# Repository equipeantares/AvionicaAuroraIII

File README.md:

AAA                                                                                                      IIIIIIIIIIIIIIIIIIIIIIIIIIIIII
              A:::A                                                                                                     I::::::::II::::::::II::::::::I
             A:::::A                                                                                                    I::::::::II::::::::II::::::::I
            A:::::::A                                                                                                   II::::::IIII::::::IIII::::::II
           A:::::::::A        uuuuuu    uuuuuu rrrrr   rrrrrrrrr      ooooooooooo   rrrrr   rrrrrrrrr   aaaaaaaaaaaaa     I::::I    I::::I    I::::I  
          A:::::A:::::A       u::::u    u::::u r::::rrr:::::::::r   oo:::::::::::oo r::::rrr:::::::::r  a::::::::::::a    I::::I    I::::I    I::::I  
         A:::::A A:::::A      u::::u    u::::u r:::::::::::::::::r o:::::::::::::::or:::::::::::::::::r aaaaaaaaa:::::a   I::::I    I::::I    I::::I  
        A:::::A   A:::::A     u::::u    u::::u rr::::::rrrrr::::::ro:::::ooooo:::::orr::::::rrrrr::::::r         a::::a   I::::I    I::::I    I::::I  
       A:::::A     A:::::A    u::::u    u::::u  r:::::r     r:::::ro::::o     o::::o r:::::r     r:::::r  aaaaaaa:::::a   I::::I    I::::I    I::::I  
      A:::::AAAAAAAAA:::::A   u::::u    u::::u  r:::::r     rrrrrrro::::o     o::::o r:::::r     rrrrrrraa::::::::::::a   I::::I    I::::I    I::::I  
     A:::::::::::::::::::::A  u::::u    u::::u  r:::::r            o::::o     o::::o r:::::r           a::::aaaa::::::a   I::::I    I::::I    I::::I  
    A:::::AAAAAAAAAAAAA:::::A u:::::uuuu:::::u  r:::::r            o::::o     o::::o r:::::r          a::::a    a:::::a   I::::I    I::::I    I::::I  
   A:::::A             A:::::Au:::::::::::::::uur:::::r            o:::::ooooo:::::o r:::::r          a::::a    a:::::a II::::::IIII::::::IIII::::::II
  A:::::A               A:::::Au:::::::::::::::ur:::::r            o:::::::::::::::o r:::::r          a:::::aaaa::::::a I::::::::II::::::::II::::::::I
 A:::::A                 A:::::Auu::::::::uu:::ur:::::r             oo:::::::::::oo  r:::::r           a::::::::::aa:::aI::::::::II::::::::II::::::::I
AAAAAAA                   AAAAAAA uuuuuuuu  uuuurrrrrrr               ooooooooooo    rrrrrrr            aaaaaaaaaa  aaaaIIIIIIIIIIIIIIIIIIIIIIIIIIIIII

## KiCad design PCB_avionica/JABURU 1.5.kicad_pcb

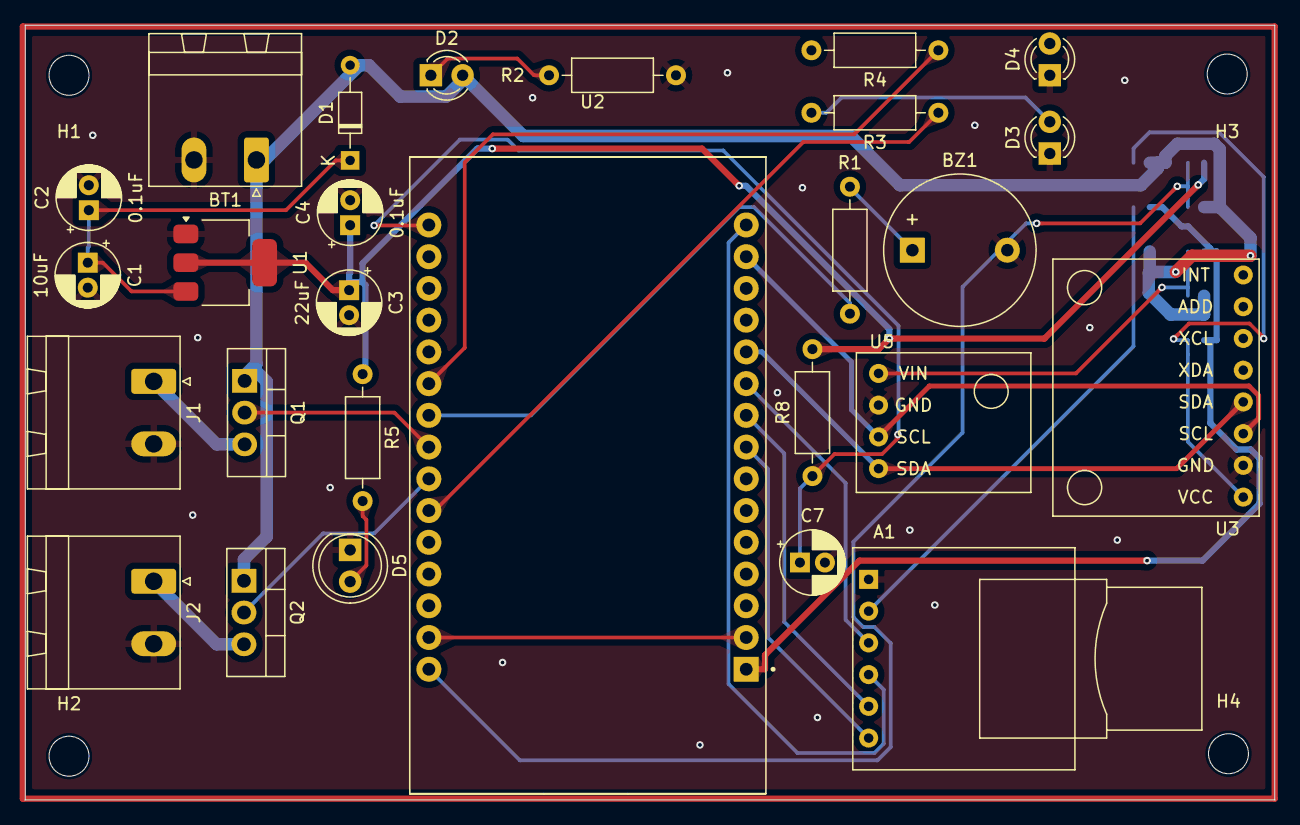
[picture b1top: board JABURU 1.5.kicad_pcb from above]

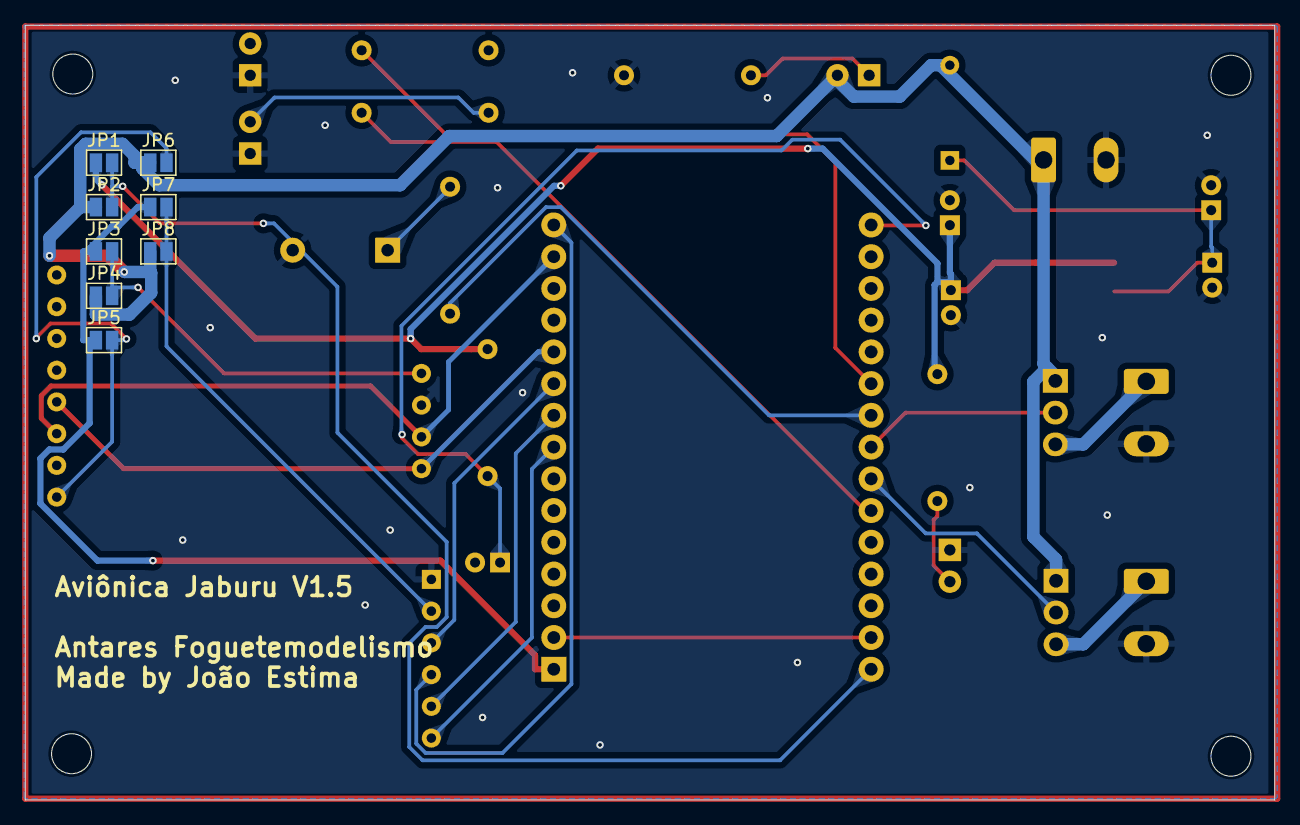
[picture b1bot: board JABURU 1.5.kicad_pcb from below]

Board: 2 copper layers, 100.0 x 62.0 mm, 39 parts (8 on the bottom side), 29 nets.

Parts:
A1: SD_Card_Module
BT1: Battery_Cell; PhoenixContact_MSTBA_2,5_2-G_1x02_P5.00mm_Horizontal
BZ1: Buzzer; Buzzer_12x9.5RM7.6
C1: 10uF; CP_Radial_D5.0mm_P2.00mm
C2, C4, C7: 0.1uF; CP_Radial_D5.0mm_P2.00mm
C3: 22uF; CP_Radial_D5.0mm_P2.00mm
D1: D; D_DO-34_SOD68_P7.62mm_Horizontal
D2: Red; LED_D3.0mm
D3: Yellow; LED_D3.0mm
D4: Green; LED_D3.0mm
D5: LED; LED_D5.0mm
H1, H2, H3, H4: MountingHole; MountingHole_3.2mm_M3
J1: IGN_01; PhoenixContact_MSTBA_2,5_2-G_1x02_P5.00mm_Horizontal
J2: IGN_02; PhoenixContact_MSTBA_2,5_2-G_1x02_P5.00mm_Horizontal
JP1: LDO 3V3; SolderJumper-2_P1.3mm_Open_Pad1.0x1.5mm
JP2, JP4, JP6, JP8: BATTERY; SolderJumper-2_P1.3mm_Open_Pad1.0x1.5mm
JP3, JP5, JP7: ESP 3V3; SolderJumper-2_P1.3mm_Open_Pad1.0x1.5mm
Q1, Q2: NMOS_Substrate; TO-220-3_Vertical
R1: 100; R_Axial_DIN0207_L6.3mm_D2.5mm_P10.16mm_Horizontal
R2, R5: 220; R_Axial_DIN0207_L6.3mm_D2.5mm_P10.16mm_Horizontal
R3, R4: 125; R_Axial_DIN0207_L6.3mm_D2.5mm_P10.16mm_Horizontal
R8: 10K; R_Axial_DIN0207_L6.3mm_D2.5mm_P10.16mm_Horizontal
U1: AMS1117-3.3; SOT-223-3_TabPin2
U2: ESP32-DEVKIT-V1; MODULE_ESP32_DEVKIT_V1
U3: module_mpu6050
U5: module_bme280_alt

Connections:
+3V3: C3.1, C4.1, JP1.1 (A), R5.1, R8.2, U1.2 (VO)
+BATT: BT1.1 (+), D1.2 (A), D2.2 (A), JP2.1 (A), JP4.1 (A), JP6.1 (A), JP8.1 (A), Q1.1 (D), Q2.1 (D)
BZR: R1.1, U2.22 (D33)
CSSD: A1.6 (CS), U2.8 (D5)
GND: A1.1 (GND), BT1.2 (-), BZ1.2 (+), C1.2, C2.2, C3.2, C4.2, C7.2, D3.1 (K), D4.1 (K), D5.1 (K), J1.2, J2.2, R2.1, U1.1 (GND), U3.2 (GND), U5.2 (GND)
IGN_1: Q1.2 (G), U2.23 (D25)
IGN_2: Q2.2 (G), U2.24 (D26)
LedAcionamento: R4.1, U2.21 (D32)
LedStatus: R3.1, U2.25 (D27)
MISO: A1.3 (MISO), U2.10 (D19)
MOSI: A1.4 (MOSI), U2.15 (D23)
unnamed: A1.2 (3V3), JP7.2 (B), JP8.2 (B)
unnamed: BZ1.1 (-), R1.2
unnamed: C1.1, C2.1, D1.1 (K), U1.3 (VI)
unnamed: D2.1 (K), R2.2
unnamed: D3.2 (A), R3.2
unnamed: D4.2 (A), R4.2
unnamed: D5.2 (A), R5.2
unnamed: J1.1, Q1.3 (S)
unnamed: J2.1, Q2.3 (S)
unnamed: JP1.2 (B), JP2.2 (B), U2.30 (VIN)
unnamed: JP3.2 (B), JP4.2 (B), U5.1 (VIN)
unnamed: JP5.2 (B), JP6.2 (B), U3.1 (VCC)
unnamed: C7.1, R8.1, U2.16 (EN)
unnamed: U2.2 (GND), U2.29 (GND)
SCK: A1.5 (CLK), U2.9 (D18)
SCL: U2.14 (D22), U3.3 (SCL), U5.3 (SCL)
SDA: U2.11 (D21), U3.4 (SDA), U5.4 (SDA)
VDD: JP3.1 (A), JP5.1 (A), JP7.1 (A), U2.1 (3V3)

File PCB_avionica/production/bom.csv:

Designator,Footprint,Quantity,Value,LCSC Part #
A1,SD_Card_Module,1,SD_Card_Module,
A2,BMP280_Module,1,BMP280_Module,
BT1,"PhoenixContact_MSTBA_2,5_2-G_1x02_P5.00mm_Horizontal",1,Battery_Cell,
BZ1,Buzzer_12x9.5RM7.6,1,Buzzer,
"C1, C3",CP_Radial_D5.0mm_P2.00mm,2,10uF,
"C2, C4",CP_Radial_D5.0mm_P2.00mm,2,0.1uF,
C5,CP_Radial_D5.0mm_P2.00mm,1,100n,
D1,D_DO-34_SOD68_P7.62mm_Horizontal,1,D,
D2,LED_D3.0mm,1,Red,
D3,LED_D3.0mm,1,Yellow,
D4,LED_D3.0mm,1,Green,
D5,LED_D5.0mm,1,LED,
"H1, H2, H3, H4",MountingHole_3.2mm_M3,4,MountingHole,
"J1, J2","PhoenixContact_MSTBA_2,5_2-G_1x02_P5.00mm_Horizontal",2,Screw_Terminal_01x02,
J3,PinSocket_2x01_P2.54mm_Vertical,1,RESET,
J4,MPU6050,1,Conn_01x08_Pin,
JP1,SolderJumper-2_P1.3mm_Open_Pad1.0x1.5mm,1,LDO 3V3,
"JP2, JP4, JP6, JP8",SolderJumper-2_P1.3mm_Open_Pad1.0x1.5mm,4,BATTERY,
"JP3, JP5, JP7",SolderJumper-2_P1.3mm_Open_Pad1.0x1.5mm,3,ESP 3V3,
"Q1, Q2",TO-220-3_Vertical,2,NMOS_Substrate,
R1,R_Axial_DIN0207_L6.3mm_D2.5mm_P10.16mm_Horizontal,1,100,
"R2, R5",R_Axial_DIN0207_L6.3mm_D2.5mm_P10.16mm_Horizontal,2,220,
"R3, R4",R_Axial_DIN0207_L6.3mm_D2.5mm_P10.16mm_Horizontal,2,125,
R6,R_Axial_DIN0207_L6.3mm_D2.5mm_P10.16mm_Horizontal,1,1M,
U1,SOT-223-3_TabPin2,1,AMS1117-3.3,
U2,MODULE_ESP32_DEVKIT_V1,1,ESP32-DEVKIT-V1,

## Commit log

2024-03-24 Codigos Rugeri
    Codigo conjunto e libs adulteradas
2024-03-24 Codigos do MPU usando somente a biblioteca I2C e o codigo junto com o MPU
2024-03-25 código conjunto adafruit - sem microSD
2024-03-25 PCB-1v0_bmp280+mpu6050+microsd+dual deploy
2024-03-25 organizei as pastas
2024-03-26 Calibracao e dataframe
2024-03-28 sd, mpu e bmp
2024-04-04 Abre/fecha arquivo, identificacao de pinos
2024-04-18 Atualizacao
    Pequenas mudancas nao significativas
2024-05-01 Removida lib MPU e macros
2024-05-23 Exclusao de comandos print
2024-09-05 Ajustei o código da avionica para última
2024-09-11 Coloquei o código da célula de carga + MicroSD junto com a aviônica
2024-09-11 PCB's da aviônica e código da célula de carga
2024-09-11 Voltei a verão da rotina para última commitada pelo Rugire
2024-09-24 Aviônica Jaburu pino buzzer atualizado
2024-09-27 Update Rotina_Avionica.ino
    implementada para o esp32
2024-10-14 Aviônica com furações e MOSFET atualizados
2024-10-17 Mudanças no footprint do esp32 na aviônica - retirei os mounting holes do footprint do esp32
2024-10-21 Adicionado bypass na alimentaçção dos módulos da avionica Jaburu
2024-11-07 outline da Jaburu corrigido pra fabricação
2024-11-13 correção na diferença entre o clearence e o furo metálico que deve ser >= 0.2mm
2024-11-21 tirei qualquer pinheader com diametro menor que 2.54mm pq a fabricante não aceita
